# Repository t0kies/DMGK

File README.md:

# DMGK
DMGK is a keyboard inspired by the gameboy color. It has a slider on the side to control volume, and is designed to be modular. 
<!-- image is in images/ -->

## Features
- Volume slider
- Polycarbonate and rubber molded case
- QMK firmware

## Planned features
- Bluetooth connectivity
- USB-C
- Multidevice support
- Modularity (modules include LCD, macropad, and pinout)

## How to build
- Download the Gerber files from the releases page
- Send the Gerber files to a PCB manufacturer
- Order with placement and solder mask or do it yourself
- Flash the firmware using QMK Toolbox

## How to flash firmware
- Download the firmware from the releases page
- Open QMK Toolbox
- Select the firmware file
- Select the correct port
- Click flash

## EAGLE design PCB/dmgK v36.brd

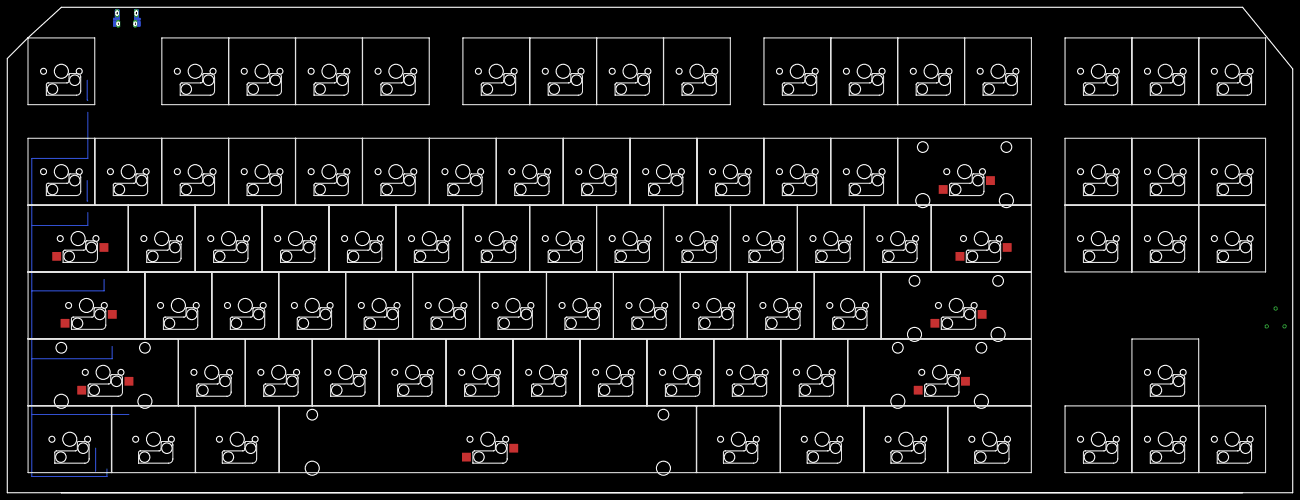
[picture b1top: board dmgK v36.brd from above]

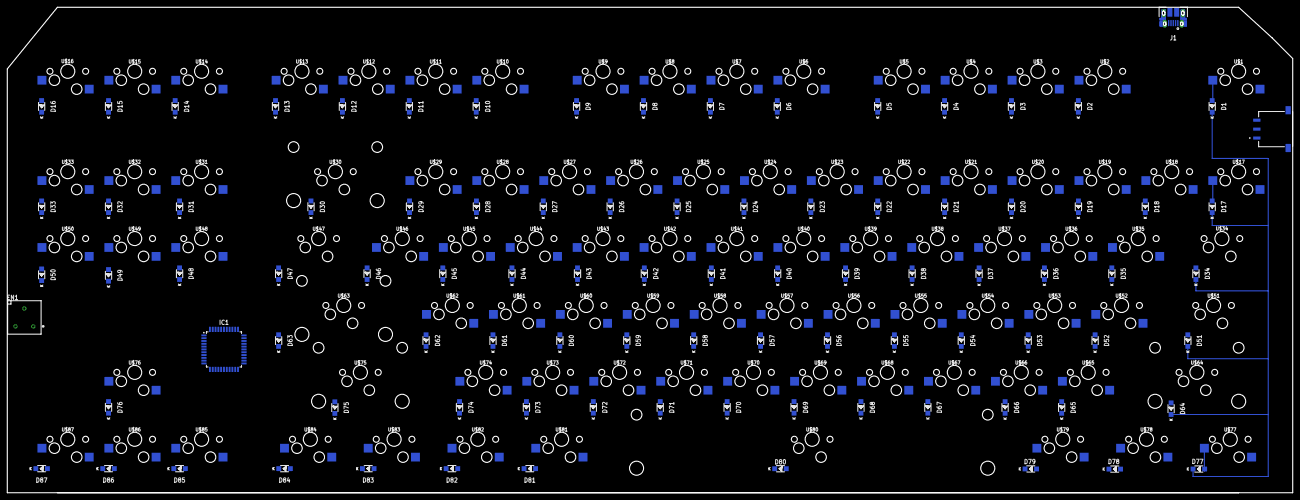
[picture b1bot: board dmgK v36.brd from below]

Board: 2 copper layers, 366.0 x 138.2 mm, 178 parts (91 on the bottom side), 112 nets.

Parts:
D1, D2, D3, D4, D5, D6, D7, D8, D9, D10, D11, D12, D13, D14, D15, D16, D17, D18, D19, D20, D21, D22, D23, D24, D25, D26, D27, D28, D29, D30, D31, D32, D33, D34, D35, D36, D37, D38, D39, D40, D41, D42, D43, D44, D45, D46, D47, D48, D49, D50, D51, D52, D53, D54, D55, D56, D57, D58, D59, D60, D61, D62, D63, D64, D65, D66, D67, D68, D69, D70, D71, D72, D73, D74, D75, D76, D77, D78, D79, D80, D81, D82, D83, D84, D85, D86, D87: DIODE; SOD-123
EN1: 3315Y-001-006L
IC1: ATMEGA16; QFP80P1200X1200X120-44
J1: 10103594
S1: ES03MSABE
U$1, U$2, U$3, U$4, U$5, U$6, U$7, U$8, U$9, U$10, U$11, U$12, U$13, U$14, U$15, U$16, U$17, U$18, U$19, U$20, U$21, U$22, U$23, U$24, U$25, U$26, U$27, U$28, U$29, U$31, U$32, U$33, U$35, U$36, U$37, U$38, U$39, U$40, U$41, U$42, U$43, U$44, U$45, U$46, U$48, U$49, U$50, U$52, U$53, U$54, U$55, U$56, U$57, U$58, U$59, U$60, U$61, U$62, U$65, U$66, U$67, U$68, U$69, U$70, U$71, U$72, U$73, U$74, U$76, U$85, U$86, U$87: KS-MXHSPCB-1.0U; MXHSPCB-1U
U$30: KS-MXHSPCB-2.0U; MXHSPCB-2U
U$34, U$47: KS-MXHSPCB-1.5U; MXHSPCB-1.5U
U$51: KS-MXHSPCB-1.75U; MXHSPCB-1.75U
U$63, U$64: KS-MXHSPCB-2.25U; MXHSPCB-2.25U
U$75: KSMXHSPCB-2.75U; MXHSPCB-2.75U
U$77, U$78, U$79, U$81, U$82, U$83, U$84: KS-MXHSPCB-1.25U; MXHSPCB-1.25U
U$80: KS-MXHSPCB-6.25U; MXHSPCB-6.25U

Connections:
GND: IC1.6, J1.5
unnamed: D1.A, U$1.MX1
unnamed: D2.A, U$2.MX1
unnamed: D3.A, U$3.MX1
unnamed: D4.A, U$4.MX1
unnamed: D5.A, U$5.MX1
unnamed: D6.A, U$6.MX1
unnamed: D7.A, U$7.MX1
unnamed: D8.A, U$8.MX1
unnamed: D9.A, U$9.MX1
unnamed: D10.A, U$10.MX1
unnamed: D11.A, U$11.MX1
unnamed: D12.A, U$12.MX1
unnamed: D13.A, U$13.MX1
unnamed: D14.A, U$14.MX1
unnamed: D15.A, U$15.MX1
unnamed: D16.A, U$16.MX1
unnamed: D17.A, U$17.MX1
unnamed: D18.A, U$18.MX1
unnamed: D19.A, U$19.MX1
unnamed: D20.A, U$20.MX1
unnamed: D21.A, U$21.MX1
unnamed: D22.A, U$22.MX1
unnamed: D23.A, U$23.MX1
unnamed: D24.A, U$24.MX1
unnamed: D25.A, U$25.MX1
unnamed: D26.A, U$26.MX1
unnamed: D27.A, U$27.MX1
unnamed: D28.A, U$28.MX1
unnamed: D29.A, U$29.MX1
unnamed: D30.A, U$30.MX1
unnamed: D31.A, U$31.MX1
unnamed: D32.A, U$32.MX1
unnamed: D33.A, U$33.MX1
unnamed: D34.A, U$34.MX1
unnamed: D35.A, U$35.MX1
unnamed: D36.A, U$36.MX1
unnamed: D37.A, U$37.MX1
unnamed: D38.A, U$38.MX1
unnamed: D39.A, U$39.MX1
unnamed: D40.A, U$40.MX1
unnamed: D41.A, U$41.MX1
unnamed: D42.A, U$42.MX1
unnamed: D43.A, U$43.MX1
unnamed: D44.A, U$44.MX1
unnamed: D45.A, U$45.MX1
unnamed: D46.A, U$46.MX1
unnamed: D47.A, U$47.MX1
unnamed: D48.A, U$48.MX1
unnamed: D49.A, U$49.MX1
unnamed: D50.A, U$50.MX1
unnamed: D51.A, U$51.MX1
unnamed: D52.A, U$52.MX1
unnamed: D53.A, U$53.MX1
unnamed: D54.A, U$54.MX1
unnamed: D55.A, U$55.MX1
unnamed: D56.A, U$56.MX1
unnamed: D57.A, U$57.MX1
unnamed: D58.A, U$58.MX1
unnamed: D59.A, U$59.MX1
unnamed: D60.A, U$60.MX1
unnamed: D61.A, U$61.MX1
unnamed: D62.A, U$62.MX1
unnamed: D63.A, U$63.MX1
unnamed: D64.A, U$64.MX1
unnamed: D65.A, U$65.MX1
unnamed: D66.A, U$66.MX1
unnamed: D67.A, U$67.MX1
unnamed: D68.A, U$68.MX1
unnamed: D69.A, U$69.MX1
unnamed: D70.A, U$70.MX1
unnamed: D71.A, U$71.MX1
unnamed: D72.A, U$72.MX1
unnamed: D73.A, U$73.MX1
unnamed: D74.A, U$74.MX1
unnamed: D75.A, U$75.MX1
unnamed: D76.A, U$76.MX1
unnamed: D77.A, U$77.MX1
unnamed: D78.A, U$78.MX1
unnamed: D79.A, U$79.MX1
unnamed: D80.A, U$80.MX1
unnamed: D81.A, U$81.MX1
unnamed: D82.A, U$82.MX1
unnamed: D83.A, U$83.MX1
unnamed: D84.A, U$84.MX1
unnamed: D85.A, U$85.MX1
unnamed: D86.A, U$86.MX1
unnamed: D87.A, U$87.MX1
unnamed: U$1.MX2, U$2.MX2, U$3.MX2, U$4.MX2, U$5.MX2, U$6.MX2, U$7.MX2, U$8.MX2, U$9.MX2, U$10.MX2, U$11.MX2, U$12.MX2, U$13.MX2, U$14.MX2, U$15.MX2, U$16.MX2
unnamed: U$17.MX2, U$18.MX2, U$19.MX2, U$20.MX2, U$21.MX2, U$22.MX2, U$23.MX2, U$24.MX2, U$25.MX2, U$26.MX2, U$27.MX2, U$28.MX2, U$29.MX2, U$30.MX2, U$31.MX2, U$32.MX2, U$33.MX2
unnamed: U$34.MX2, U$35.MX2, U$36.MX2, U$37.MX2, U$38.MX2, U$39.MX2, U$40.MX2, U$41.MX2, U$42.MX2, U$43.MX2, U$44.MX2, U$45.MX2, U$46.MX2, U$47.MX2, U$48.MX2, U$49.MX2, U$50.MX2
unnamed: U$51.MX2, U$52.MX2, U$53.MX2, U$54.MX2, U$55.MX2, U$56.MX2, U$57.MX2, U$58.MX2, U$59.MX2, U$60.MX2, U$61.MX2, U$62.MX2, U$63.MX2
unnamed: U$64.MX2, U$65.MX2, U$66.MX2, U$67.MX2, U$68.MX2, U$69.MX2, U$70.MX2, U$71.MX2, U$72.MX2, U$73.MX2, U$74.MX2, U$75.MX2, U$76.MX2
unnamed: U$77.MX2, U$78.MX2, U$79.MX2, U$80.MX2, U$81.MX2, U$82.MX2, U$83.MX2, U$84.MX2, U$85.MX2, U$86.MX2, U$87.MX2
unnamed: D33.C, D50.C, D87.C
unnamed: D16.C, D32.C, D49.C, D76.C, D86.C
unnamed: D15.C, D31.C, D48.C, D85.C
unnamed: D14.C, D30.C, D47.C
unnamed: D13.C, D29.C, D46.C, D63.C
unnamed: D12.C, D28.C, D45.C, D62.C, D75.C, D84.C
unnamed: D11.C, D27.C, D44.C, D61.C, D74.C, D83.C
unnamed: D10.C, D26.C, D43.C, D60.C, D73.C, D82.C
unnamed: D9.C, D25.C, D42.C, D59.C, D72.C, D81.C
unnamed: D8.C, D24.C, D41.C, D58.C, D71.C
unnamed: D7.C, D23.C, D40.C, D57.C, D70.C
unnamed: D6.C, D22.C, D39.C, D56.C, D69.C, D80.C
unnamed: D5.C, D21.C, D38.C, D55.C, D68.C
unnamed: D4.C, D20.C, D37.C, D54.C, D67.C
unnamed: D3.C, D19.C, D36.C, D53.C, D66.C, D79.C
unnamed: D2.C, D18.C, D35.C, D52.C, D65.C, D78.C
unnamed: D1.C, D17.C, D34.C, D51.C, D64.C, D77.C
VCC: IC1.5, J1.1

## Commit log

2022-12-06 This is a step file for the render
2022-12-06 OBJ rendered
2022-12-06 re-organized
2022-12-07 case stl uploaded
2022-12-07 renders updated
2022-12-07 Firmware, Schematics, Footprint
2022-12-07 Updated Readme file
    Updated Readme file
2022-12-07 image update
